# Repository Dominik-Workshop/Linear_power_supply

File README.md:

# Linear power supply

> [!CAUTION]
> This project was initiated in 2021 when my skills were more limited. As a result, there might be areas for improvement. I occasionally enhance both the performance and readability of project files for better understanding.

### More info about this project can be found on my channel: 
 https://youtu.be/JCxF-o6tLgA

## Used tools:
 &nbsp;&nbsp;&nbsp;&nbsp; &nbsp;&nbsp;&nbsp;&nbsp; 
&nbsp;&nbsp;&nbsp;&nbsp; &nbsp;&nbsp;&nbsp;&nbsp; &nbsp;&nbsp;&nbsp;&nbsp; &nbsp;&nbsp;&nbsp;&nbsp; 
#

## Project Overview
- Homemade linear power supply capable of delivering up to 250W (0-28V, 0.01-10A)
- Features adjustable voltage and current limit, controlled by 10-turn potentiometers.
- Incorporates an on/off switch for convenient power control.
- Utilizes a relay transformer-tab switching circuit to minimize power losses by reducing the voltage differential across the linear regulator.
- Enhanced heat dissipation through a temperature-controlled fan cooling the heatsink.

> [!IMPORTANT]
> I changed the Q1 transistor from IRF9530 (P-MOSFET) to BD912 (PNP-BJT) to greatly improve the stability of this power supply and completely eliminate oscillations in the constant current mode. (Their pinouts match, so it is a drop-in replacement)
> <details>
> <summary>Click to learn more</summary>
> After performing some simulations in LTspice, I figured out that simply changing the Q1 MOSFET to a BJT greatly improved the output response to input step:
>
> Before (with MOSFET):
> <image src="images/screenshots/old_step.png">
> After (with BJT):
> <image src="images/screenshots/new_step.png">
> (The bode plot also looks better)
> </details>

## Output Measurements
Output voltage waveforms before changing Q1 to a BJT can be found in measurements.pdf

## Project details
I used this 12 300VA transformer, which I slightly modified. The secondary winding consisted of 4 wires connected in parallel. I split them in 2 and connected in series, getting 24V with a center tap). Last but not least, I added another winding of around 8V.

I used an old graphics card's heatsink for cooling.

It was based on SN1534 power supply, its schematics can be found there as well.

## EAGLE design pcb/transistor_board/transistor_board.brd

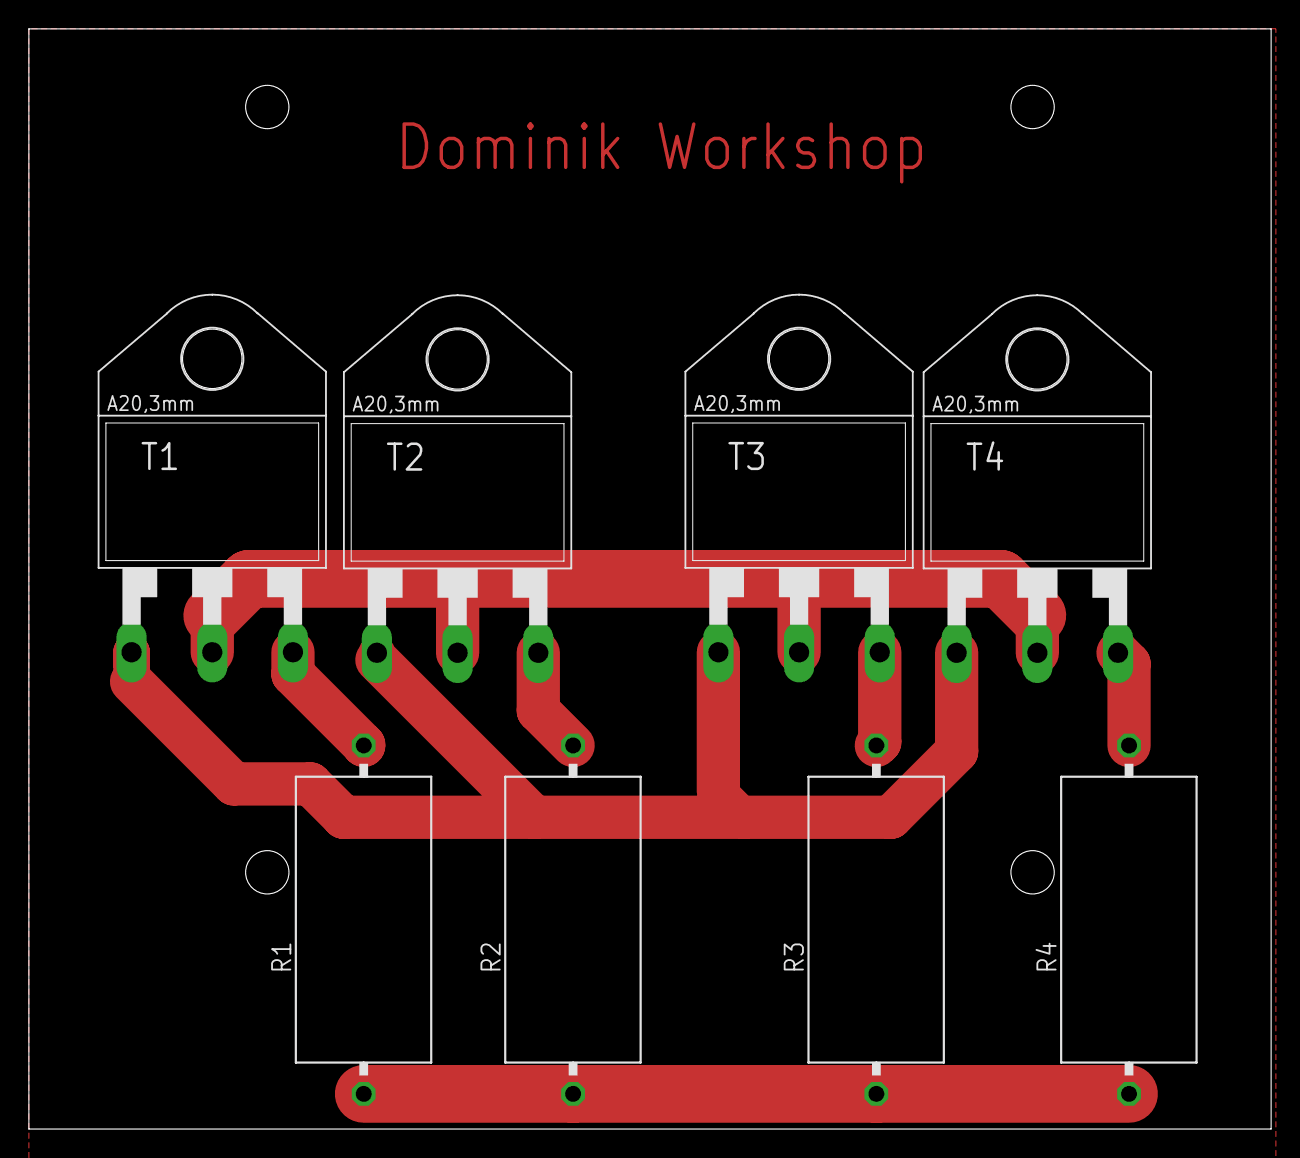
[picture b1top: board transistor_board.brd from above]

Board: 2 copper layers, 86.0 x 76.2 mm, 8 parts (0 on the bottom side), 7 nets.

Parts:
R1, R2, R3, R4: VTA53
T1, T2, T3, T4: BD249; TOP3

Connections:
unnamed: R1.2, T1.3
unnamed: R2.2, T2.3
unnamed: R3.2, T3.3
unnamed: R1.1, R2.1, R3.1, R4.1
unnamed: T1.2, T2.2, T3.2, T4.2
unnamed: T1.1, T2.1, T3.1, T4.1
unnamed: R4.2, T4.3

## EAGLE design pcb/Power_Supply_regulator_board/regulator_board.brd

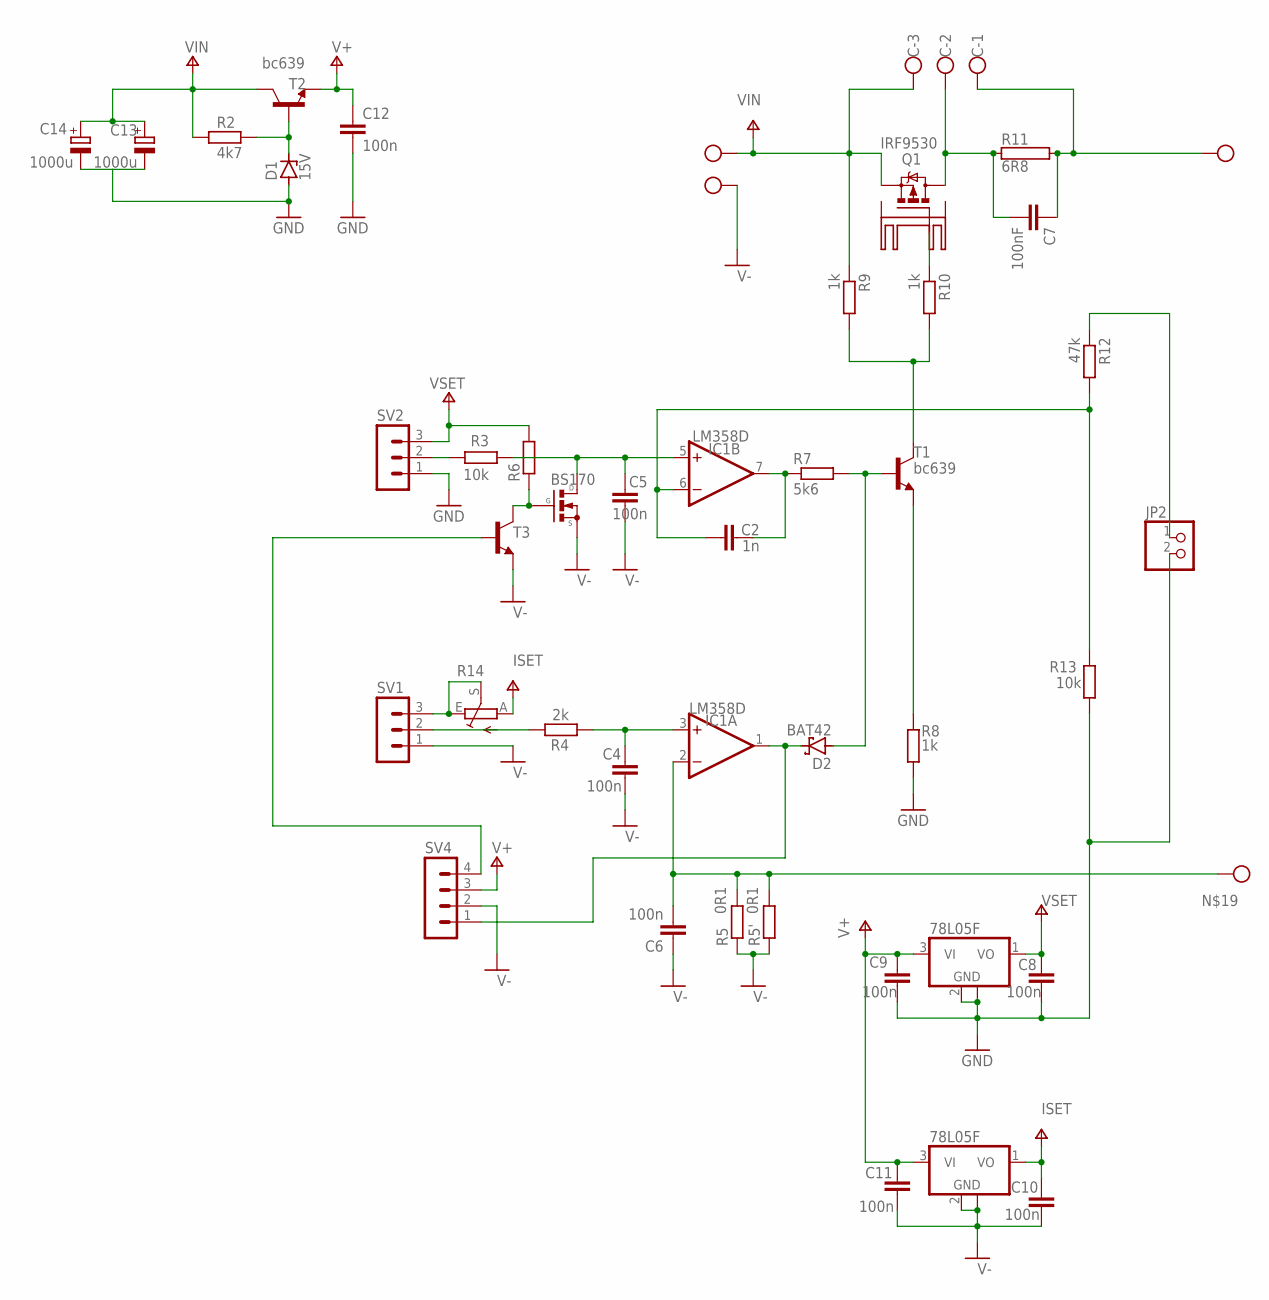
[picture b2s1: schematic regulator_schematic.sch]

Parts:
C: W237-103
C2: 1n; C0805
C4, C5, C6, C8, C9, C10, C11: 100n; C0805
C7: 100nF; C0805
C12: 100n; C075-032X103
C13, C14: 1000u; E7,5-16
D1: 15V; DO34Z7
D2: BAT42; DO35-10
IC1: LM358D; SO08
IC2, IC3: 78L05F; SOT89
JP2: PINHD-1X2; 1X02
KK1: SK104-PAD
Q1: IRF9530; TO220BV
Q3: BS170; SOT54ES
R2: 4k7; R0805
R3, R13: 10k; R0805
R4: 2k; 0204/7
R5, R5': 0R1; VTA52
R6: R-EU_R0805; R0805
R7: 5k6; 0204/7
R8: 1k; R0805
R9, R10: 1k; 0204/7
R11: 6R8; MNS-5
R12: 47k; R0805
R14: TRIM_EU-B64Y; B64Y
SV1, SV2: MA03-1
SV4: MA04-1
T1, T2: bc639; TO92-ECB
T3: BC817-16-NPN-SOT23-BEC; SOT23-BEC
X1, X2: W237-102

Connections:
GND: C8.1, C9.1, IC2.2 (GND), IC2.2@1 (GND), JP2.2, R13.2, SV2.1
ISET: C10.2, IC3.1 (VO), R14.A
unnamed: D2.C, IC1.1 (OUT), SV4.1
unnamed: C5.2, IC1.5 (+IN), Q3.D, R3.1
unnamed: C4.2, IC1.3 (+IN), R4.1
unnamed: C2.2, IC1.7 (OUT), R7.1
unnamed: D2.A, R7.2, T1.B
unnamed: R8.2, T1.E
unnamed: C2.1, IC1.6 (-IN), R12.2, R13.1
unnamed: R3.2, SV2.2
unnamed: C.2, C7.2, Q1.D, R11.1
unnamed: C.1, C7.1, R11.2, X1.2
unnamed: R14.E, R14.S, SV1.3
unnamed: R4.2, SV1.2
unnamed: D1.C, R2.2, T2.B
unnamed: Q3.G, R6.1, T3.C
unnamed: Q1.G, R10.1
unnamed: SV4.4, T3.B
unnamed: R9.2, R10.2, T1.C
unnamed: JP2.1, R12.1
unnamed: C6.2, IC1.2 (-IN), R5.2, R5'.2, X1.1
V+: C9.2, C11.2, C12.1, IC1.8 (V+), IC2.3 (VI), IC3.3 (VI), SV4.3, T2.E
V-: C4.1, C5.1, C6.1, C10.1, C11.1, C12.2, C13.-, C14.-, D1.A, IC1.4 (V-), IC3.2 (GND), IC3.2@1 (GND), Q3.S, R5.1, R5'.1, R8.1, SV1.1, SV4.2, T3.E, X2.2
VIN: C.3, C13.+, C14.+, Q1.S, R2.1, R9.1, T2.C, X2.1
VSET: C8.2, IC2.1 (VO), R6.2, SV2.3

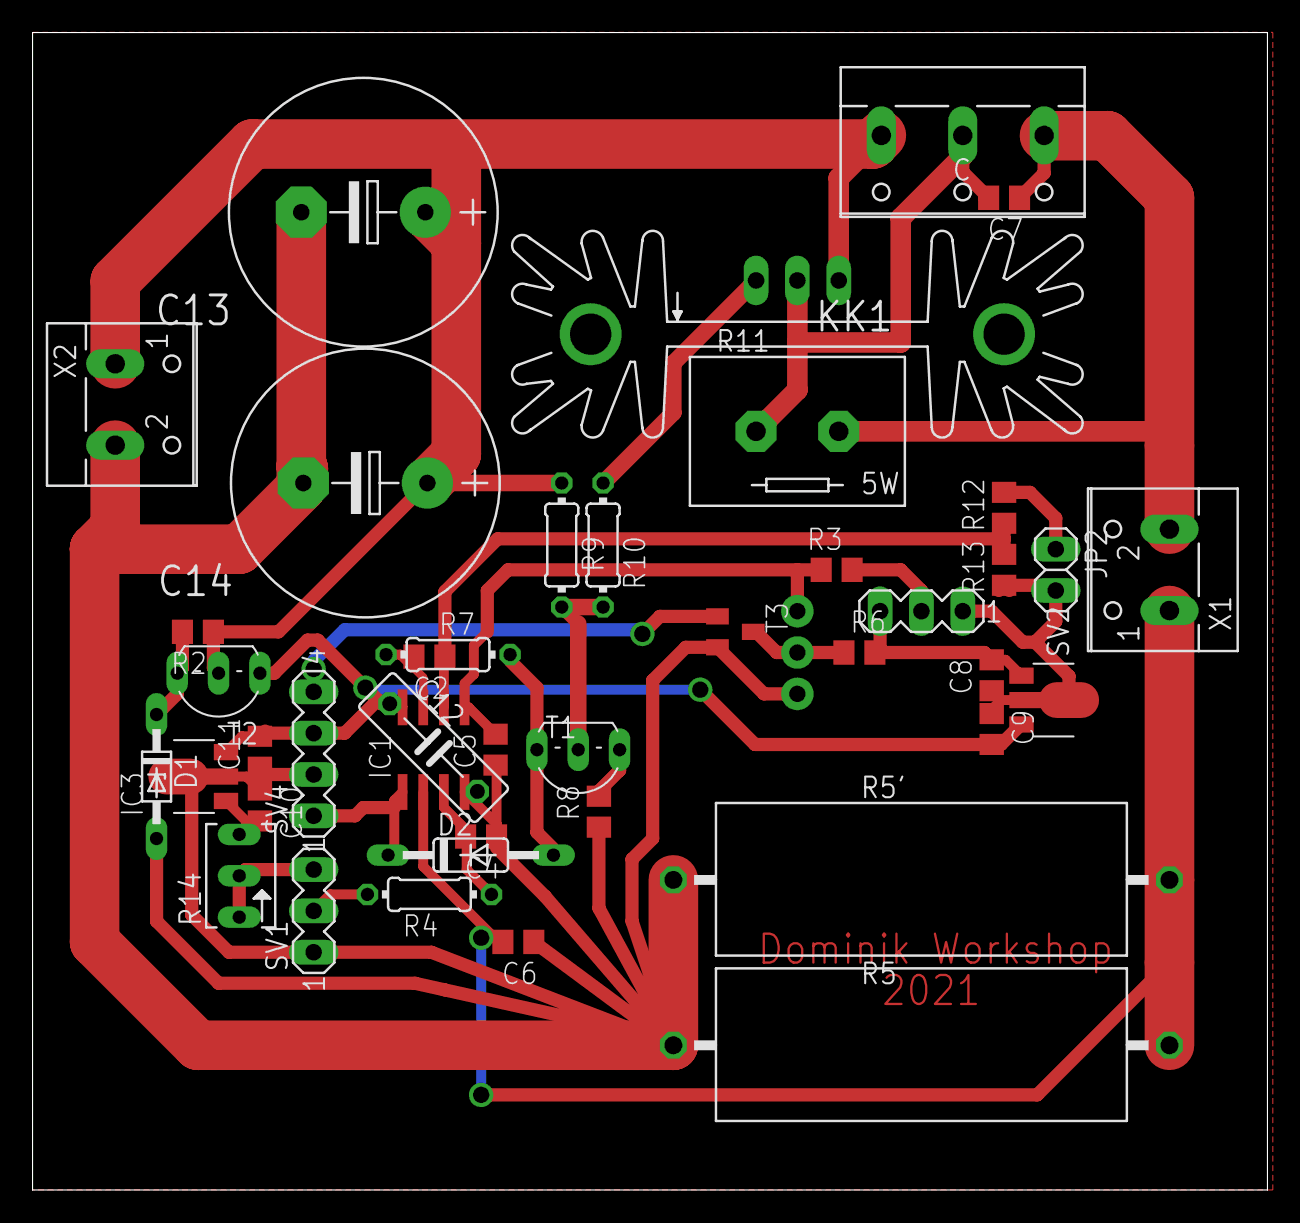
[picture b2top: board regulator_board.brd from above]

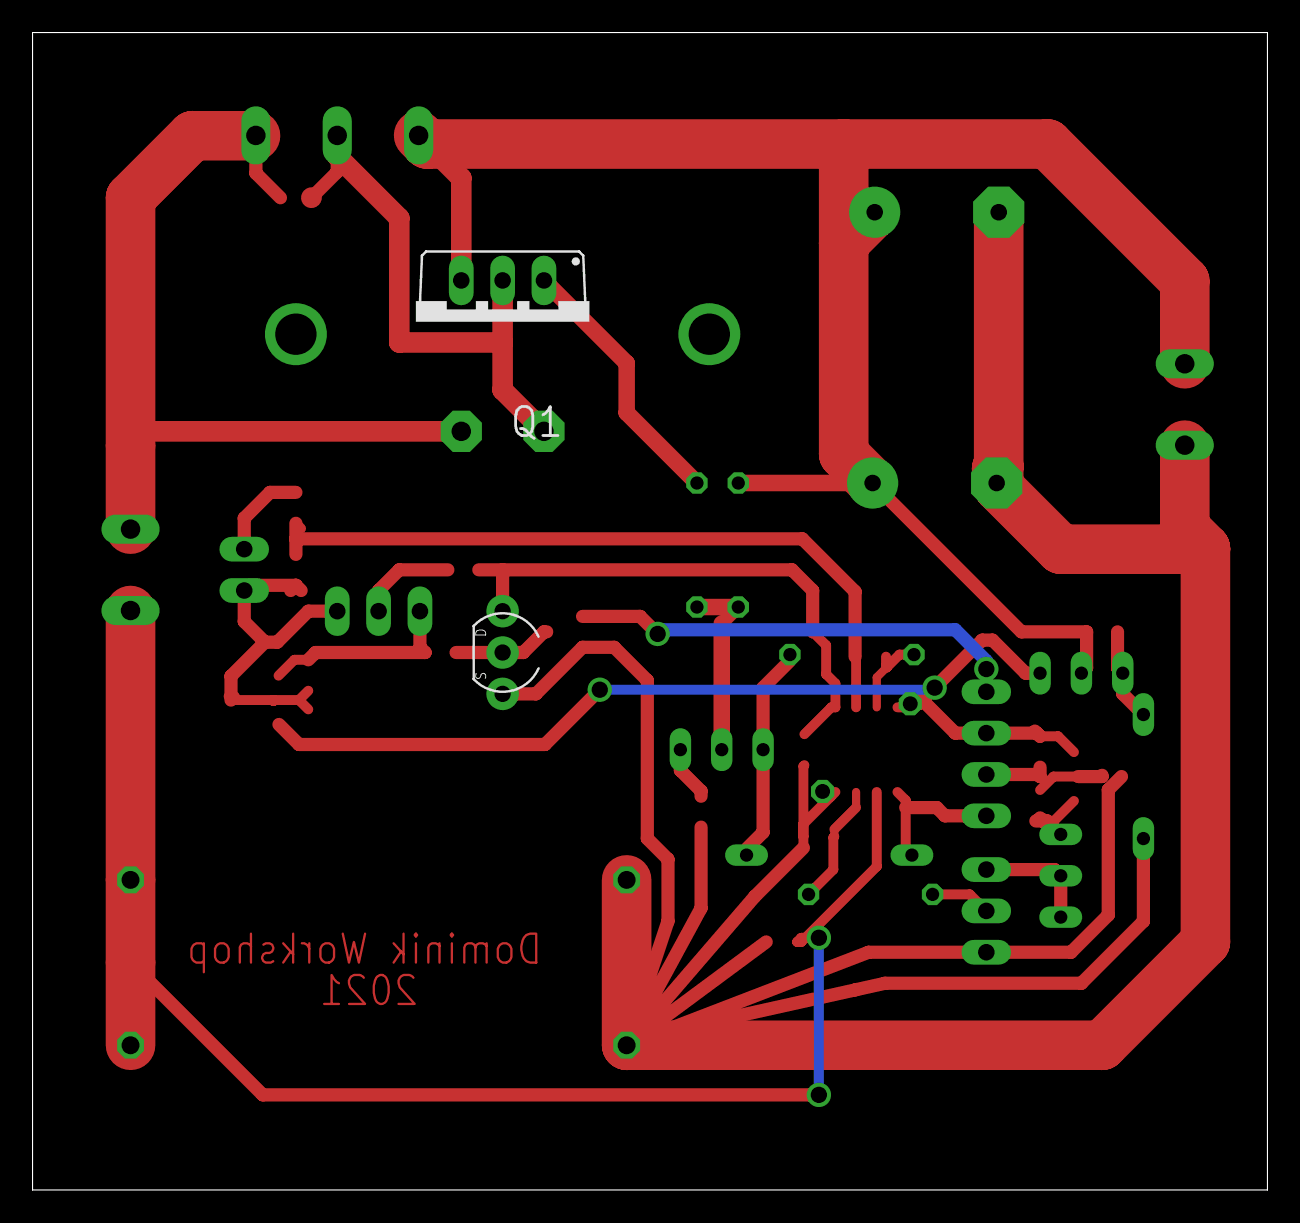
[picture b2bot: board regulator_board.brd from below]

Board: 2 copper layers, 75.9 x 71.1 mm, 44 parts (2 on the bottom side), 25 nets.

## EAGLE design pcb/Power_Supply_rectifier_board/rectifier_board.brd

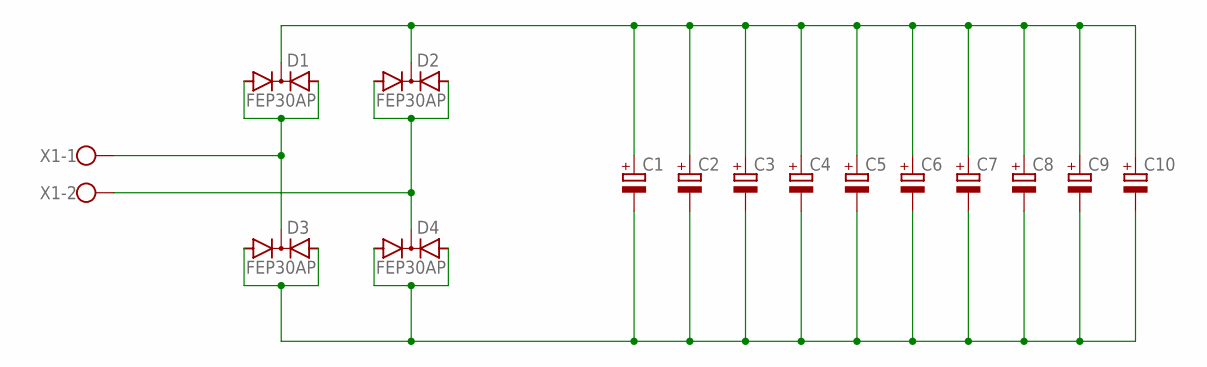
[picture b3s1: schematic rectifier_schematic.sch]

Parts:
C1, C2, C3, C4, C5, C6, C7, C8, C9, C10: CPOL-EUE7.5-18; E7,5-18
D1, D2, D3, D4: FEP30AP; TO3P
X1: W237-102

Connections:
unnamed: D1.1 (A1), D1.3 (A2), D3.2 (C), X1.1
unnamed: D2.1 (A1), D2.3 (A2), D4.2 (C), X1.2
unnamed: C1.-, C2.-, C3.-, C4.-, C5.-, C6.-, C7.-, C8.-, C9.-, C10.-, D3.1 (A1), D3.3 (A2), D4.1 (A1), D4.3 (A2)
unnamed: C1.+, C2.+, C3.+, C4.+, C5.+, C6.+, C7.+, C8.+, C9.+, C10.+, D1.2 (C), D2.2 (C)

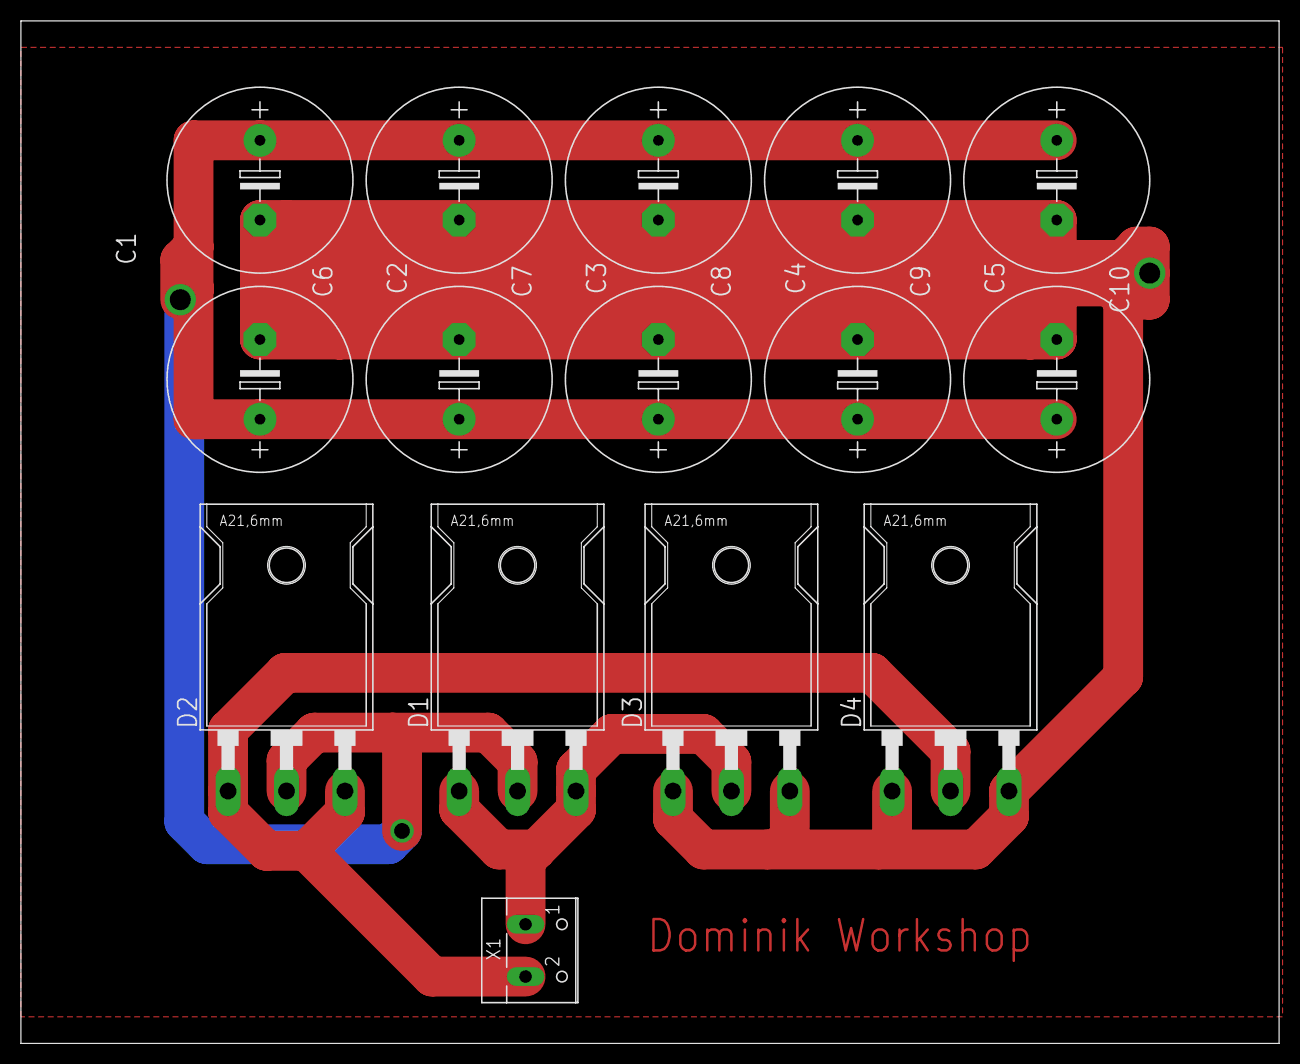
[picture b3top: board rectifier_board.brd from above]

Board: 2 copper layers, 120.3 x 97.8 mm, 15 parts (0 on the bottom side), 4 nets.

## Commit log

2022-02-28 scheme
2022-02-28 renamed schematic
2022-02-28 psu arduino code
2022-02-28 schematic on which this psu was based
2022-04-26 Eagle files of pcbs
2022-04-26 pdf for homemade pcbs (already mirrored)
2022-05-17 added missing label U_REF
2022-08-05 added YT link
2023-02-20 renamed folders
2023-02-21 measurements
2023-02-25 added transient response measurement
2024-02-09 sim v0
2024-02-09 sim v1
2024-02-09 mv v1 folder
2024-05-13 update sim
2024-05-13 resize logo
2024-12-17 Fix typos in README
